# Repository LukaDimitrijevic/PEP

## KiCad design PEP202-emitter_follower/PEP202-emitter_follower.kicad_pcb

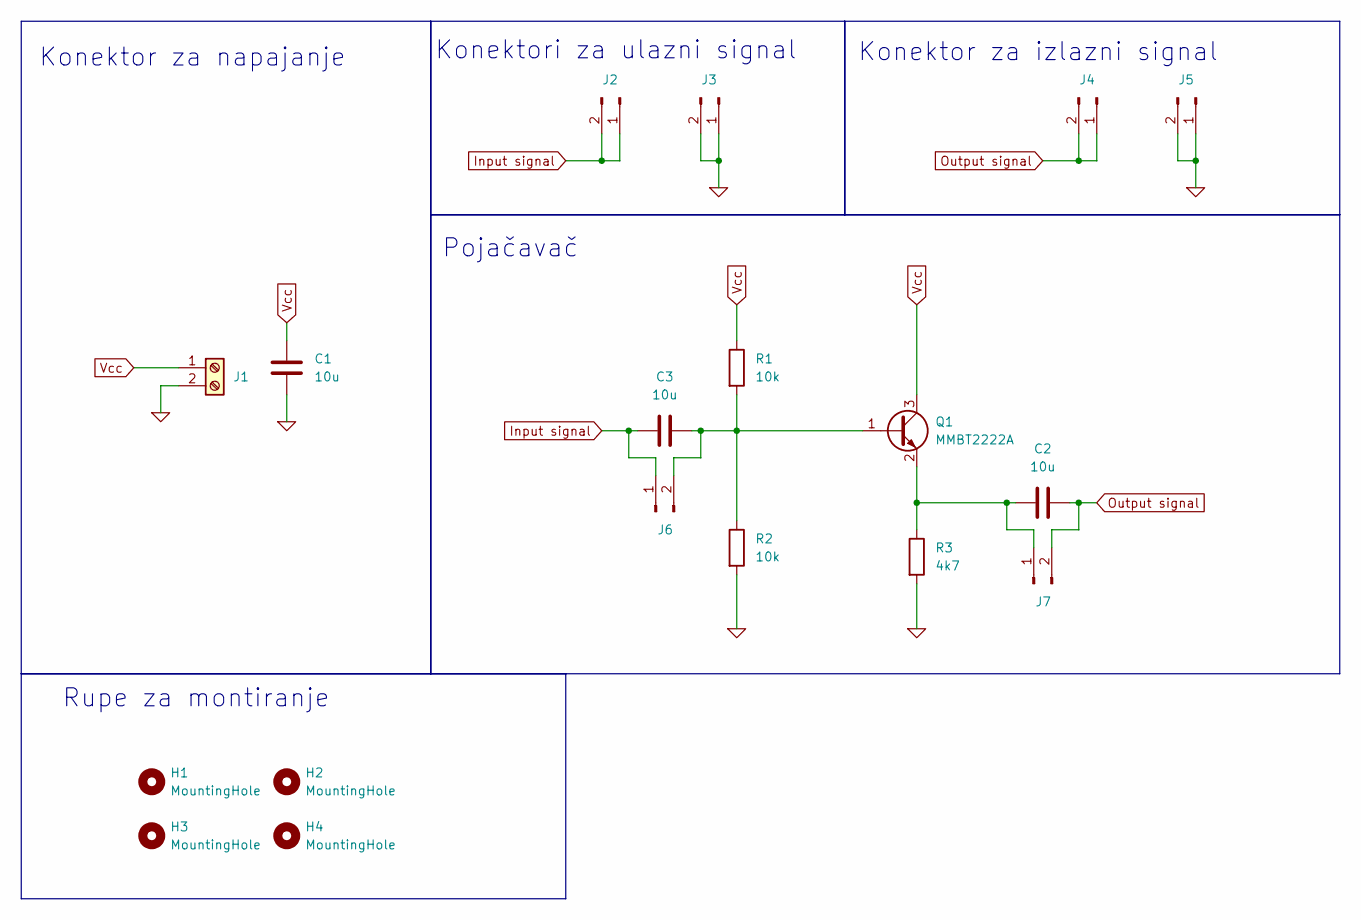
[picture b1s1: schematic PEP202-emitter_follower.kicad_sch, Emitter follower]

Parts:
C1, C2, C3: 10u; C_1206_3216Metric_Pad1.33x1.80mm_HandSolder
H1, H2, H3, H4: MountingHole; MountingHole_3.2mm_M3_ISO14580_Pad_TopBottom
J1: Screw_Terminal_01x02; TerminalBlock_Phoenix_MKDS-1,5-2-5.08_1x02_P5.08mm_Horizont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
J2, J3, J4, J5, J6, J7: Conn_01x02_Pin; PinHeader_2x01_P2.54mm_Vertical
Q1: MMBT2222A; SOT-23
R1, R2: 10k; R_1206_3216Metric_Pad1.30x1.75mm_HandSolder
R3: 4k7; R_1206_3216Metric_Pad1.30x1.75mm_HandSolder

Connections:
0: C1.1, J1.2, J3.1, J3.2, J5.1, J5.2, R2.2, R3.2
Input signal: C3.1, J2.1, J2.2, J6.1
unnamed: C3.2, J6.2, Q1.1 (B), R1.2, R2.1
unnamed: C2.1, J7.1, Q1.2 (E), R3.1
Output signal: C2.2, J4.1, J4.2, J7.2
Vcc: C1.2, J1.1, Q1.3 (C), R1.1

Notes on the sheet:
Rupe za montiranje
Konektor za izlazni signal
Konektor za napajanje
Pojačavač
Konektori za ulazni signal

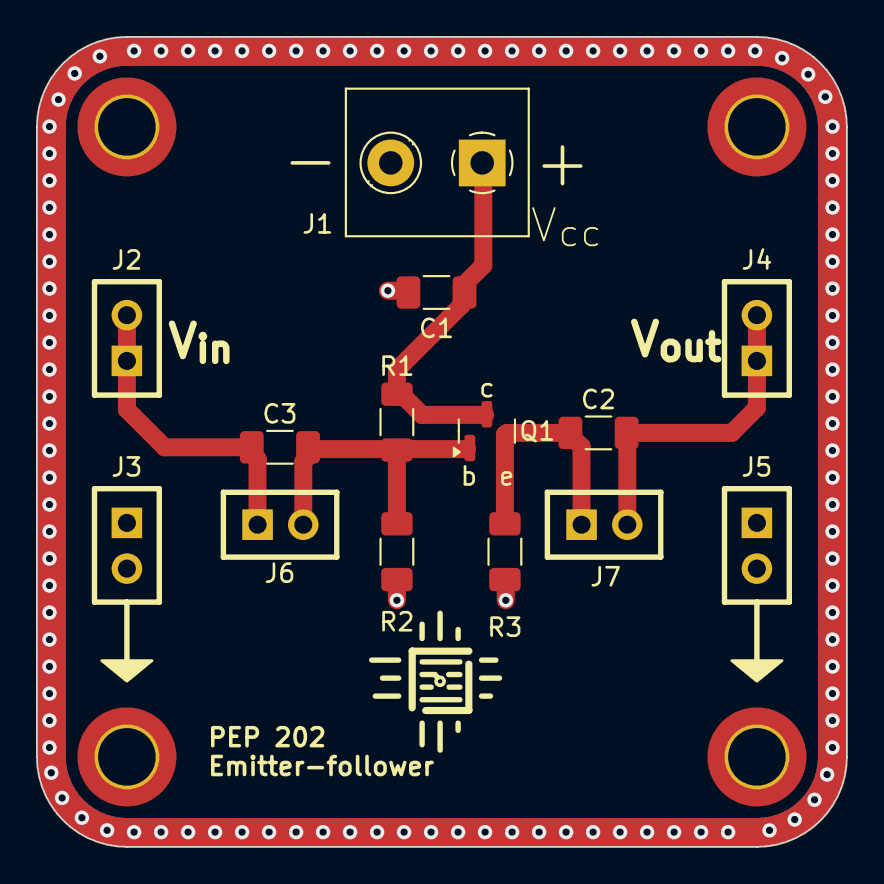
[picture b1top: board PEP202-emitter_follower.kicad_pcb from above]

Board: 2 copper layers, 45.0 x 45.0 mm, 18 parts (0 on the bottom side), 6 nets.

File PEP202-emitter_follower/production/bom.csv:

Designator,Footprint,Quantity,Value,LCSC Part #
"C1, C2, C3",1206,3,10u,
"H1, H2, H3, H4",MountingHole_3.2mm_M3_ISO14580_Pad_TopBottom,4,MountingHole,
J1,"TerminalBlock_Phoenix_MKDS-1,5-2-5.08_1x02_P5.08mm_Horizontal",1,Screw_Terminal_01x02,
"J2, J3, J4, J5, J6, J7",PinHeader_2x01_P2.54mm_Vertical,6,Conn_01x02_Pin,
Q1,SOT-23,1,MMBT2222A,
"R1, R2",1206,2,10k,
R3,1206,1,4k7,

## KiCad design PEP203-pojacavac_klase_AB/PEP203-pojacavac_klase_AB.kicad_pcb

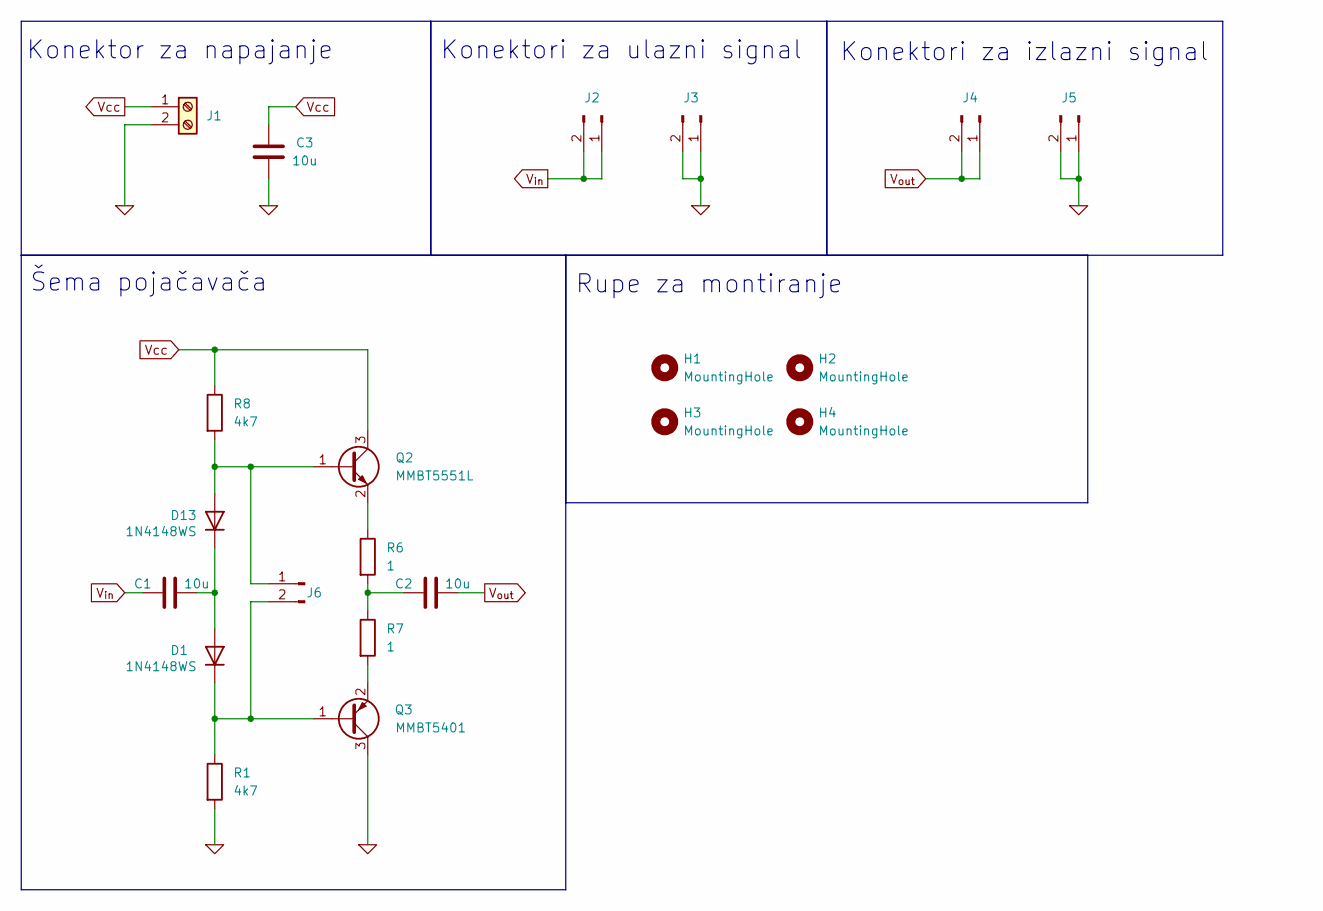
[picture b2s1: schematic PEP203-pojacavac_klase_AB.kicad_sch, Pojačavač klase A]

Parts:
C1, C2, C3: 10u; C_1206_3216Metric_Pad1.33x1.80mm_HandSolder; LCSC C13585
D1, D13: 1N4148WS; D_SOD-323; LCSC C2128
H1, H2, H3, H4: MountingHole; MountingHole_3.2mm_M3_ISO14580_Pad_TopBottom
J1: Screw_Terminal_01x02; TerminalBlock_Phoenix_MKDS-1,5-2-5.08_1x02_P5.08mm_Horizont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
J2, J3, J4, J5, J6: Conn_01x02_Pin; PinHeader_2x01_P2.54mm_Vertical
Q2: MMBT5551L; SOT-23; LCSC C2145
Q3: MMBT5401; SOT-23; LCSC C8326
R1, R8: 4k7; R_1206_3216Metric_Pad1.30x1.75mm_HandSolder; LCSC C17936
R6, R7: 1; R_1206_3216Metric_Pad1.30x1.75mm_HandSolder; LCSC C17928

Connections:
0: C3.2, J1.2, J3.1, J3.2, J5.1, J5.2, Q3.3 (C), R1.2
unnamed: C2.1, R6.2, R7.1
unnamed: C1.2, D1.2 (A), D13.1 (K)
unnamed: D1.1 (K), J6.2, Q3.1 (B), R1.1
unnamed: D13.2 (A), J6.1, Q2.1 (B), R8.2
unnamed: Q2.2 (E), R6.1
unnamed: Q3.2 (E), R7.2
V_{in}: C1.1, J2.1, J2.2
V_{out}: C2.2, J4.1, J4.2
Vcc: C3.1, J1.1, Q2.3 (C), R8.1

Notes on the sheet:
Rupe za montiranje
Konektori za izlazni signal
Konektor za napajanje
Šema pojačavača
Konektori za ulazni signal

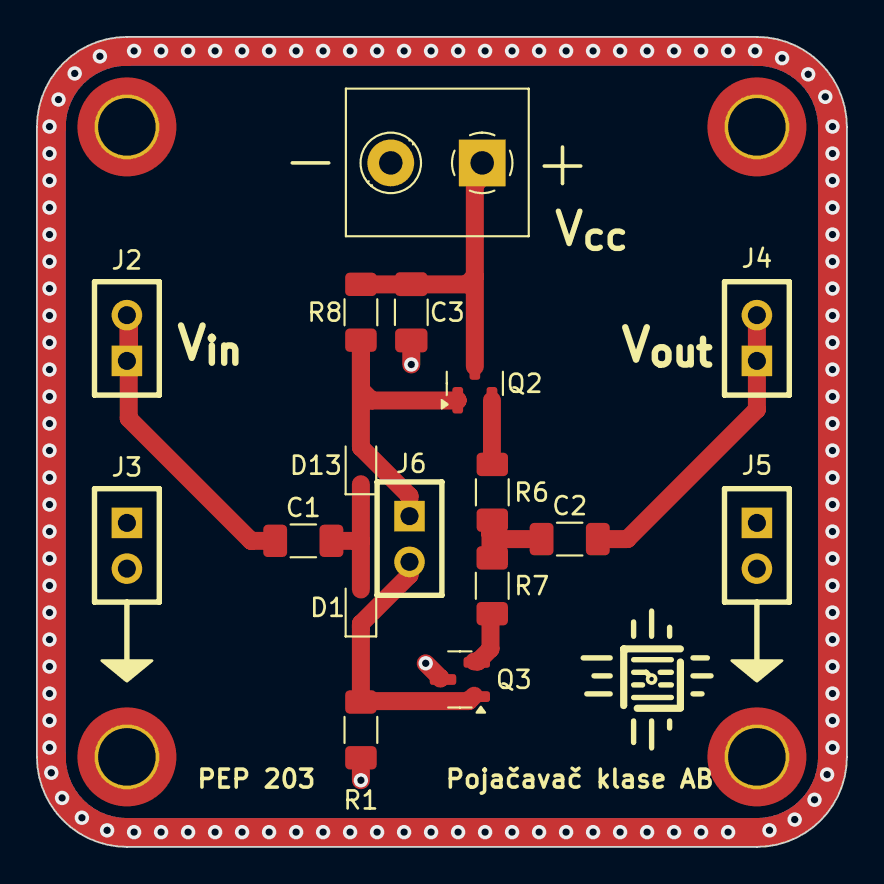
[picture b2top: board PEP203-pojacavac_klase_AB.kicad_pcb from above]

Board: 2 copper layers, 45.0 x 45.0 mm, 21 parts (0 on the bottom side), 10 nets.

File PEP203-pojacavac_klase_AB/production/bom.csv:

Designator,Footprint,Quantity,Value,LCSC Part #
"_2, ",f3223f44-050f-45ab-bded-9586cede3436,2,,
"C1, C2, C3",1206,3,10u,C13585
"D1, D13",D_SOD-323,2,1N4148WS,C2128
"H1, H2, H3, H4",MountingHole_3.2mm_M3_ISO14580_Pad_TopBottom,4,MountingHole,
J1,"TerminalBlock_Phoenix_MKDS-1,5-2-5.08_1x02_P5.08mm_Horizontal",1,Screw_Terminal_01x02,
"J2, J3, J4, J5, J6",PinHeader_2x01_P2.54mm_Vertical,5,Conn_01x02_Pin,
Q2,SOT-23,1,MMBT5551L,C2145
Q3,SOT-23,1,MMBT5401,C8326
"R1, R8",1206,2,4k7,C17936
"R6, R7",1206,2,1,C17928

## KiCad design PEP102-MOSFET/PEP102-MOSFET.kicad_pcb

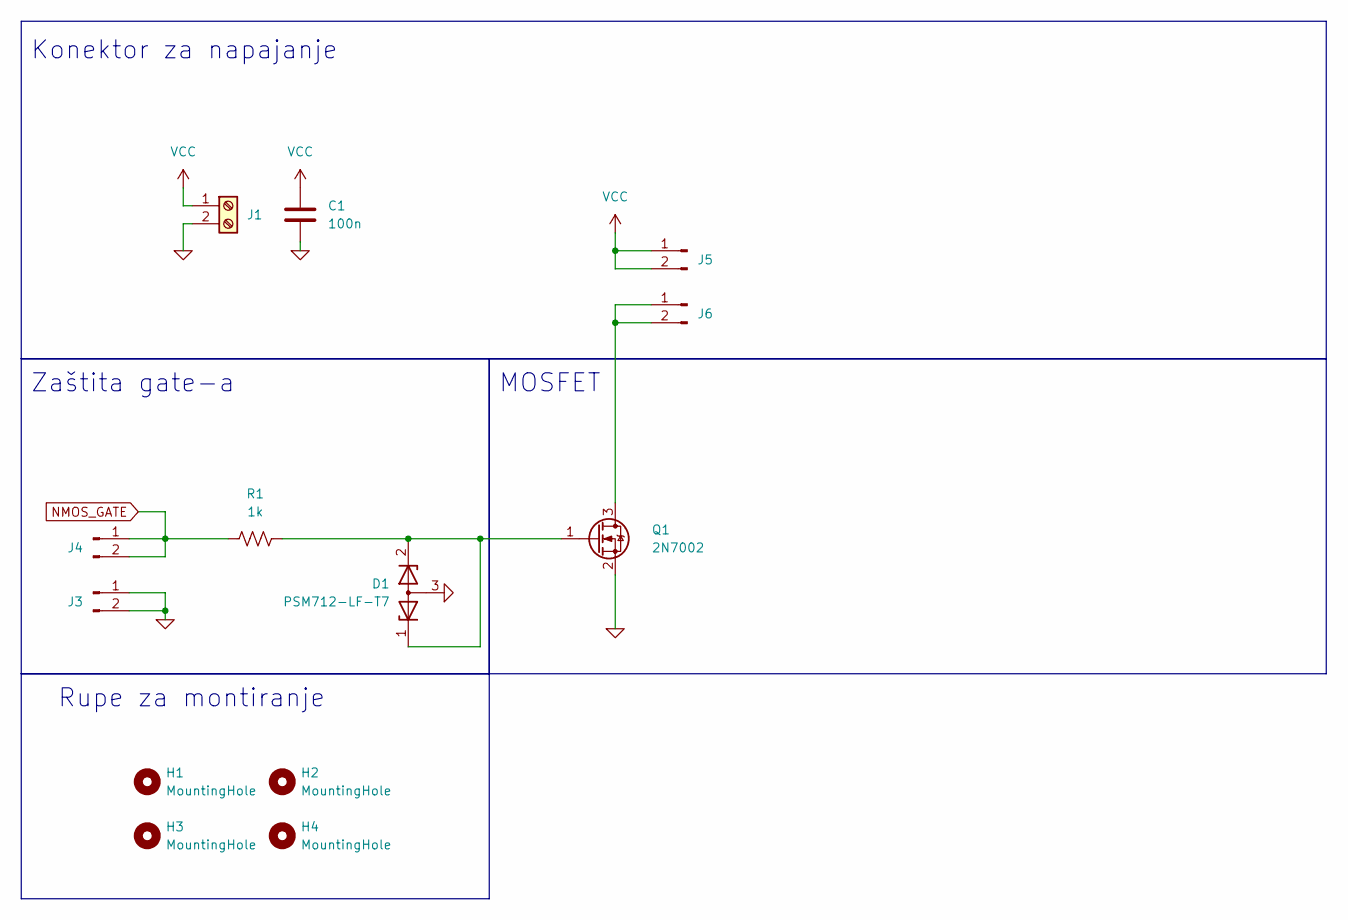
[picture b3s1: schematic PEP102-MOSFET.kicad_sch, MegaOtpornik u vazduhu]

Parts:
C1: 100n; C_1206_3216Metric_Pad1.33x1.80mm_HandSolder; LCSC C24497
D1: PSM712-LF-T7; SOT-23; LCSC C32677
H1, H2, H3, H4: MountingHole; MountingHole_3.2mm_M3_ISO14580_Pad_TopBottom
J1: Screw_Terminal_01x02; TerminalBlock_Phoenix_MKDS-1,5-2-5.08_1x02_P5.08mm_Horizont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
J3, J4, J5, J6: Conn_01x02_Pin; PinHeader_2x01_P2.54mm_Vertical
Q1: 2N7002; SOT-23; LCSC C8545
R1: 1k; R_1206_3216Metric_Pad1.30x1.75mm_HandSolder; LCSC C4410

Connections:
0: C1.2, D1.3 (A), J1.2, J3.1, J3.2, Q1.2 (S); also elsewhere on the board
NMOS_GATE: J4.1, J4.2, R1.1
unnamed: J6.1, J6.2, Q1.3 (D)
unnamed: D1.1 (K), D1.2 (K), Q1.1 (G), R1.2
VCC: C1.1, J1.1, J5.1, J5.2; also elsewhere on the board

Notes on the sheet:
Zaštita gate-a
Rupe za montiranje
Konektor za napajanje
MOSFET

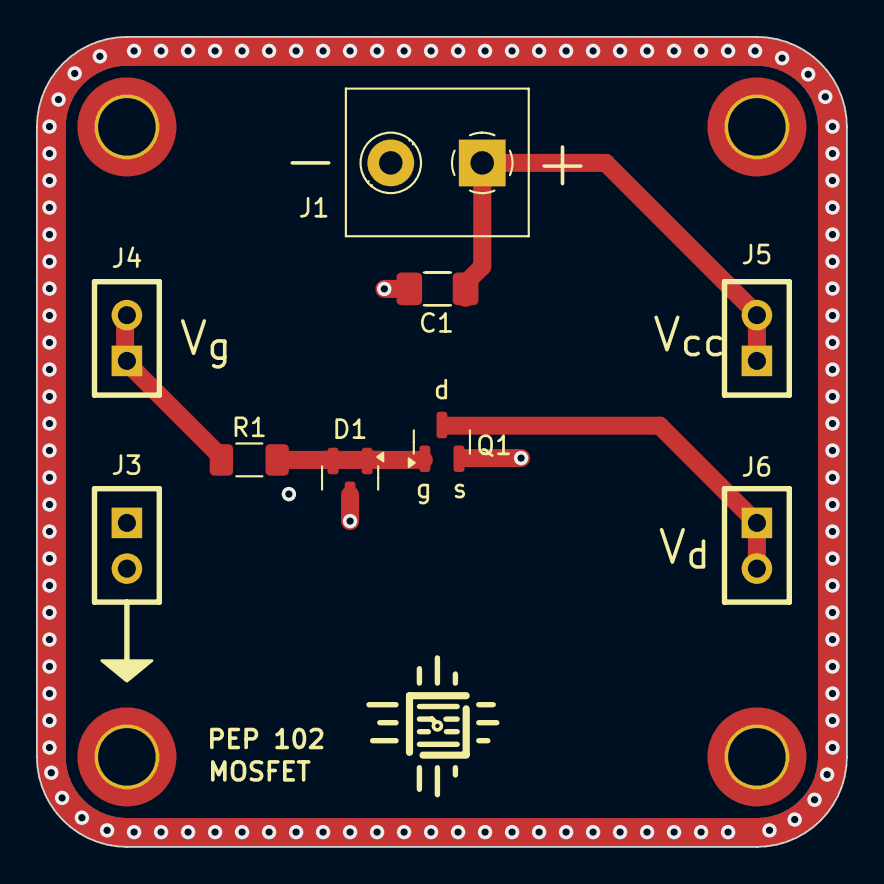
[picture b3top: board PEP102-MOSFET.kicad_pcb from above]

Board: 2 copper layers, 45.0 x 45.0 mm, 14 parts (0 on the bottom side), 5 nets.

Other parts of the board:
C1#2: 100n; C_1206_3216Metric_Pad1.33x1.80mm_HandSolder

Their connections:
0: C1#2.2; also elsewhere on the board
VCC: C1#2.1; also elsewhere on the board

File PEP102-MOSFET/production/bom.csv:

Designator,Footprint,Quantity,Value,LCSC Part #
"C1_2, C1",1206,2,100n,C24497
D1,SOT-23,1,PSM712-LF-T7,C32677
"H1, H2, H3, H4",MountingHole_3.2mm_M3_ISO14580_Pad_TopBottom,4,MountingHole,
J1,"TerminalBlock_Phoenix_MKDS-1,5-2-5.08_1x02_P5.08mm_Horizontal",1,Screw_Terminal_01x02,
"J3, J4, J5, J6",PinHeader_2x01_P2.54mm_Vertical,4,Conn_01x02_Pin,
Q1,SOT-23,1,2N7002,C8545
R1,1206,1,1k,C4410

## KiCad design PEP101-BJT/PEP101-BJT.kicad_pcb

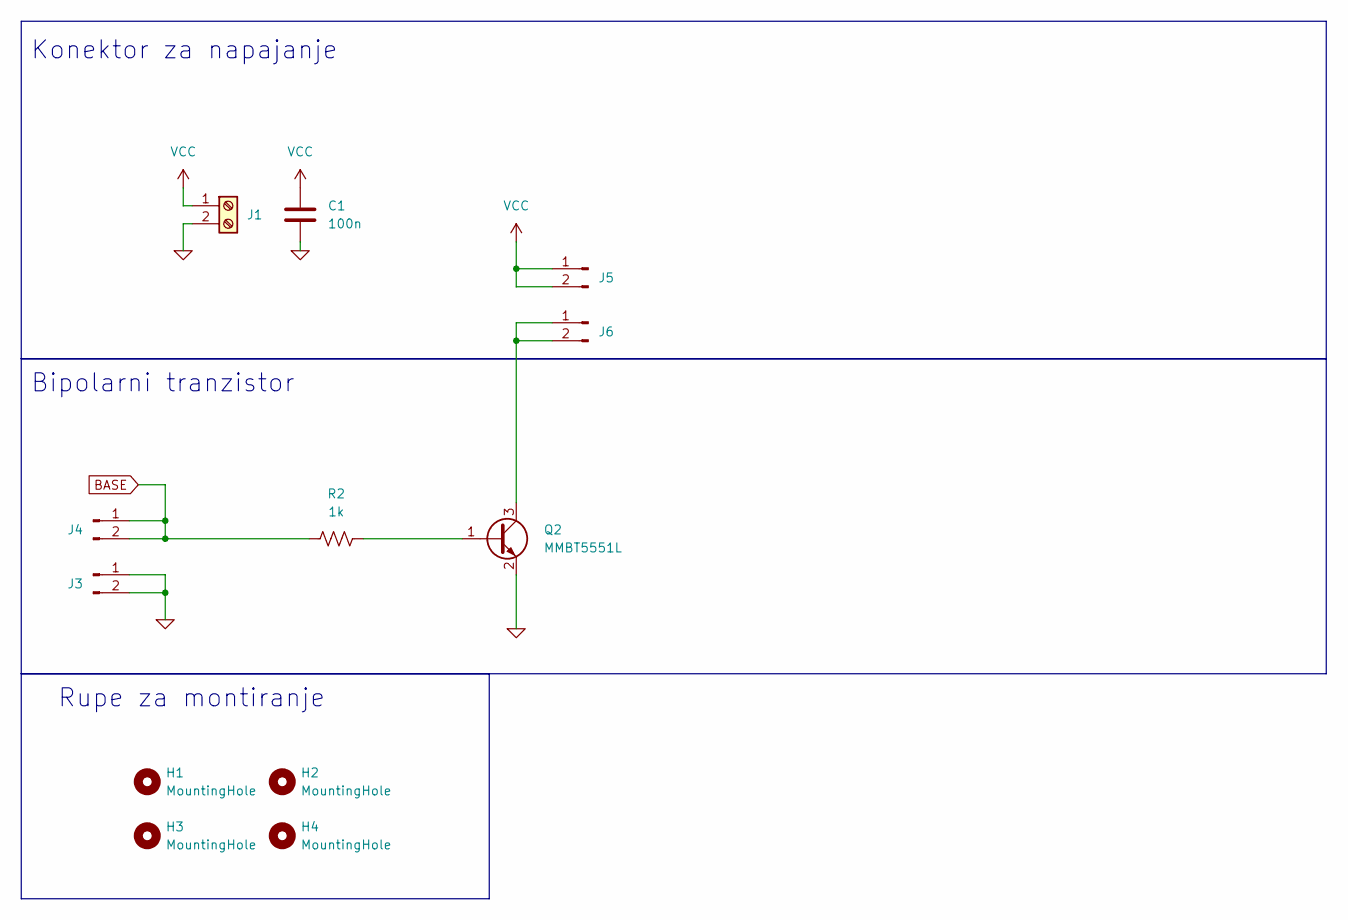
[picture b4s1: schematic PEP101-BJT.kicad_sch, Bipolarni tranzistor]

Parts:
C1: 100n; C_1206_3216Metric_Pad1.33x1.80mm_HandSolder; LCSC C24497
H1, H2, H3, H4: MountingHole; MountingHole_3.2mm_M3_ISO14580_Pad_TopBottom
J1: Screw_Terminal_01x02; TerminalBlock_Phoenix_MKDS-1,5-2-5.08_1x02_P5.08mm_Horizont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
J3, J4, J5, J6: Conn_01x02_Pin; PinHeader_2x01_P2.54mm_Vertical
Q2: MMBT5551L; SOT-23; LCSC C2145
R2: 1k; R_1206_3216Metric_Pad1.30x1.75mm_HandSolder; LCSC C4410

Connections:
0: C1.2, J1.2, J3.1, J3.2, Q2.2 (E)
BASE: J4.1, J4.2, R2.1
unnamed: J6.1, J6.2, Q2.3 (C)
unnamed: Q2.1 (B), R2.2
VCC: C1.1, J1.1, J5.1, J5.2

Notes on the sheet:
Bipolarni tranzistor
Rupe za montiranje
Konektor za napajanje

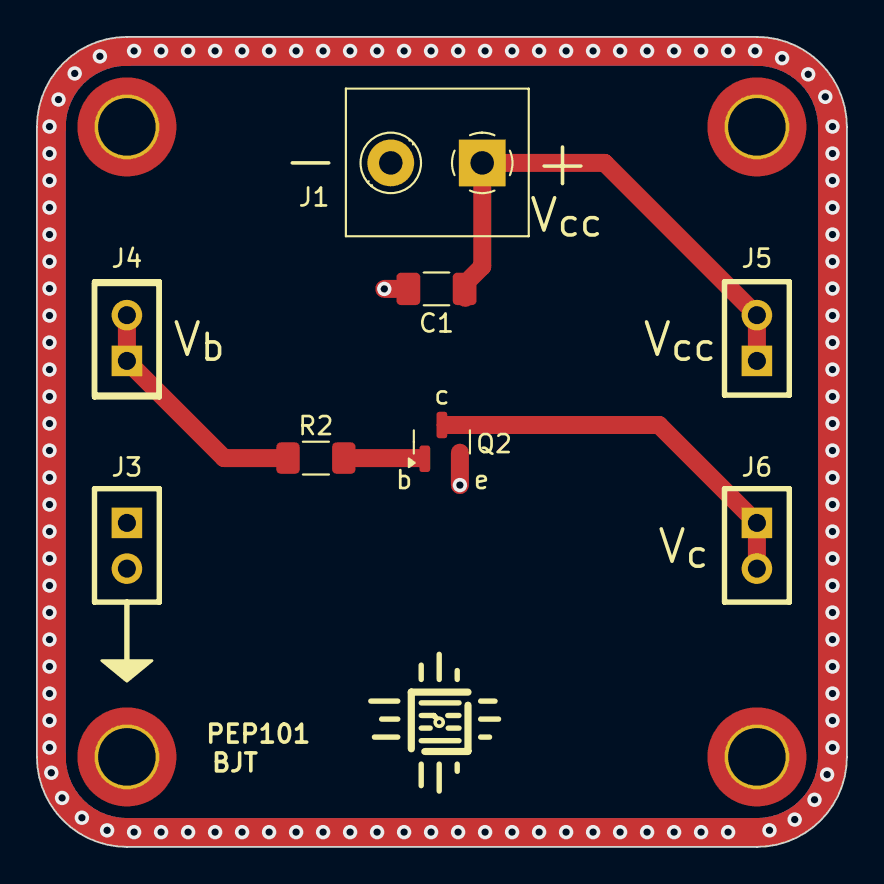
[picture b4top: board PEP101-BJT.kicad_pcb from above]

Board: 2 copper layers, 45.0 x 45.0 mm, 12 parts (0 on the bottom side), 5 nets.

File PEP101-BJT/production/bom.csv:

Designator,Footprint,Quantity,Value,LCSC Part #
C1,1206,1,100n,C24497
"H1, H2, H3, H4",MountingHole_3.2mm_M3_ISO14580_Pad_TopBottom,4,MountingHole,
J1,"TerminalBlock_Phoenix_MKDS-1,5-2-5.08_1x02_P5.08mm_Horizontal",1,Screw_Terminal_01x02,
"J3, J4, J5, J6",PinHeader_2x01_P2.54mm_Vertical,4,Conn_01x02_Pin,
Q2,SOT-23,1,MMBT5551L,C2145
R2,1206,1,1k,C4410

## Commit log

2026-03-19 fix 202
2026-03-29 dodata sim
